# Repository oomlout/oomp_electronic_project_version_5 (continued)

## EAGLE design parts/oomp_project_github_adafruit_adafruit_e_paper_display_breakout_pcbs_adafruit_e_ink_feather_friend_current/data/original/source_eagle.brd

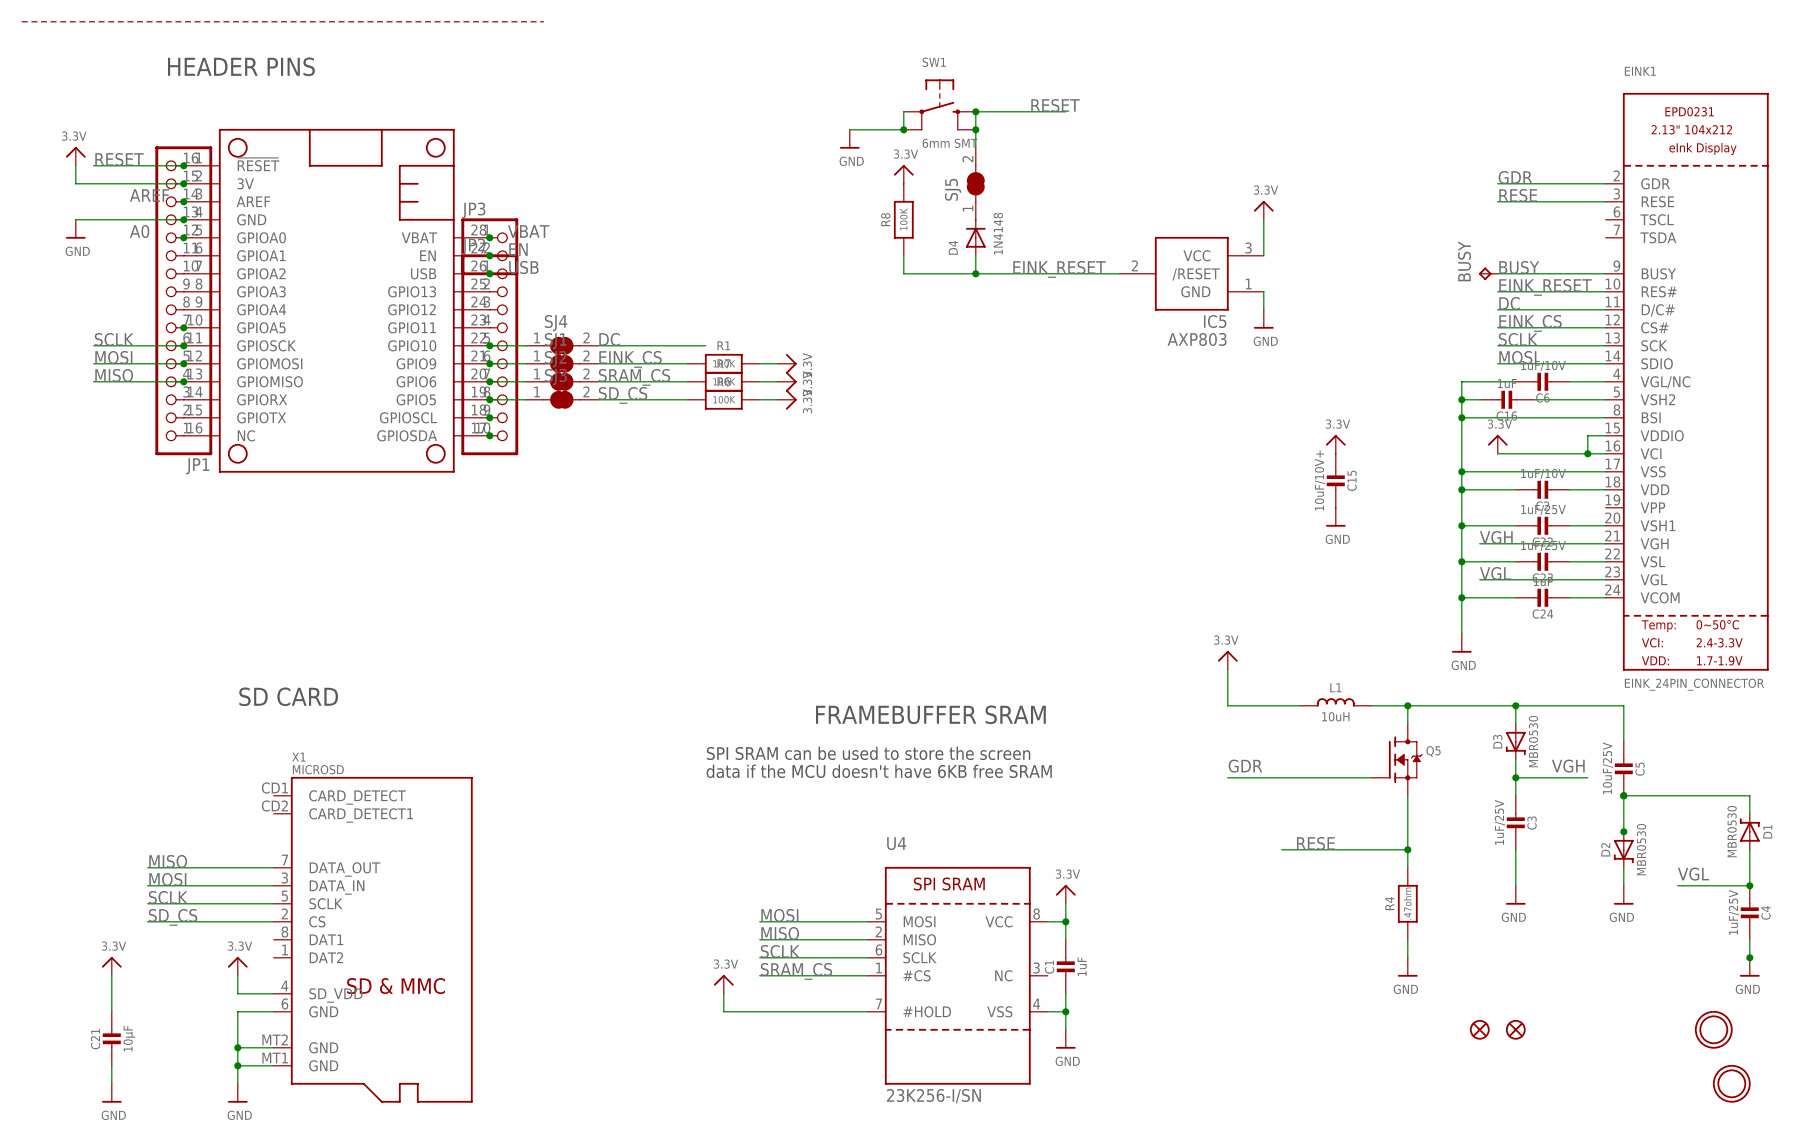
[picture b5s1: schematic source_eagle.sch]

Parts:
BUSY: TPTP15SQ; TP15SQ
C1: 1uF; 0805_10MGAP
C2, C6: 1uF/10V; 0805-NO
C3, C4, C22, C23: 1uF/25V; 0805-NO
C5: 10uF/25V; 0805-NO
C15: 10uF/10V+; 0805-NO
C16, C24: 1uF; 0805-NO
C21: 10µF; 0805-NO
D1, D2, D3: MBR0530; SOD-123
D4: 1N4148; SOD-323F
EINK1: EINK_24PIN_CONNECTOR; EINK_24PIN
FID1, FID3: FIDUCIAL_1MM
IC5: AXP803; SOT23
JP1: HEADER-1X16ROUND; 1X16_ROUND
JP2: HEADER-1X10ROUND; 1X10_ROUND
JP3: HEADER-1X2ROUND; 1X02_ROUND
L1: 10uH; INDUCTOR_4X4MM_NR401
MS1: FEATHERWING_NOHOLES
Q5: IRLML0100; SOT23-3
R1, R6, R7, R8: 100K; 0603-NO
R4: .47ohm; 0805_10MGAP
SJ1, SJ2, SJ3, SJ4, SJ5: SOLDERJUMPER_CLOSED; SOLDERJUMPER_CLOSEDWIRE
SW1: 6mm SMT; BTN_KMR2_4.6X2.8
U4: 23K256-I/SN; SOIC8_150MIL
U$3, U$4: MOUNTINGHOLE2.5; MOUNTINGHOLE_2.5_PLATED
X1: MICROSD

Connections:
3.3V: C1.1, C15.2, C21.1, EINK1.15 (VDDIO), EINK1.16 (VCI), IC5.3 (VCC), JP1.15, L1.P$2 (2), MS1.2 (3V), R1.2, R6.2, R7.2, R8.2, U4.7 (#HOLD), U4.8 (VCC), X1.4 (SD_VDD)
A0: JP1.12, MS1.5 (GPIOA0)
AREF: JP1.14, MS1.3 (AREF)
BUSY: BUSY.TP, EINK1.9 (BUSY)
DC: EINK1.11 (D/C#), SJ4.2
EINK_CS: EINK1.12 (CS#), R1.1, SJ1.2
EINK_RESET: D4.A, EINK1.10 (RES#), IC5.2 (/RESET), R8.1
EN: JP3.2, MS1.27 (EN)
GDR: EINK1.2 (GDR), Q5.1 (G)
GND: C1.2, C2.1, C3.2, C4.2, C6.1, C15.1, C16.1, C21.2, C22.1, C23.1, C24.1, D2.C, EINK1.8 (BSI), EINK1.17 (VSS), IC5.1 (GND), JP1.13, MS1.4 (GND), R4.2, SW1.A, SW1.A' (P1), U4.4 (VSS), X1.6 (GND), X1.MT1 (GND), X1.MT2 (GND)
H: JP2.8, MS1.19 (GPIO5), SJ3.1
I: JP2.7, MS1.20 (GPIO6), SJ2.1
J: JP2.6, MS1.21 (GPIO9), SJ1.1
K: JP2.5, MS1.22 (GPIO10), SJ4.1
MISO: JP1.4, MS1.13 (GPIOMISO), U4.2 (MISO), X1.7 (DATA_OUT)
MOSI: EINK1.14 (SDIO), JP1.5, MS1.12 (GPIOMOSI), U4.5 (MOSI), X1.3 (DATA_IN)
unnamed: JP1.7, MS1.10 (GPIOA5)
unnamed: C5.2, D1.C, D2.A
unnamed: C5.1, D3.A, L1.P$1 (1), Q5.3 (D)
unnamed: C16.2, EINK1.5 (VSH2)
unnamed: C2.2, EINK1.18 (VDD)
unnamed: C22.2, EINK1.20 (VSH1)
unnamed: D4.C, SJ5.1
unnamed: JP1.11, MS1.6 (GPIOA1)
unnamed: C6.2, EINK1.4 (VGL/NC)
unnamed: JP1.10, MS1.7 (GPIOA2)
unnamed: JP1.9, MS1.8 (GPIOA3)
unnamed: JP1.8, MS1.9 (GPIOA4)
unnamed: JP1.3, MS1.14 (GPIORX)
unnamed: JP1.2, MS1.15 (GPIOTX)
unnamed: JP1.1, MS1.16 (NC)
unnamed: JP2.10, MS1.17 (GPIOSDA)
unnamed: JP2.9, MS1.18 (GPIOSCL)
unnamed: JP2.4, MS1.23 (GPIO11)
unnamed: JP2.3, MS1.24 (GPIO12)
unnamed: JP2.2, MS1.25 (GPIO13)
unnamed: C23.2, EINK1.22 (VSL)
unnamed: C24.2, EINK1.24 (VCOM)
RESE: EINK1.3 (RESE), Q5.2 (S), R4.1
RESET: JP1.16, MS1.1 (!RESET), SJ5.2, SW1.B (S), SW1.B' (S1)
SCLK: EINK1.13 (SCK), JP1.6, MS1.11 (GPIOSCK), U4.6 (SCLK), X1.5 (SCLK)
SD_CS: R6.1, SJ3.2, X1.2 (CS)
SRAM_CS: R7.1, SJ2.2, U4.1 (#CS)
USB: JP2.1, MS1.26 (USB)
VBAT: JP3.1, MS1.28 (VBAT)
VGH: C3.1, D3.C, EINK1.21 (VGH)
VGL: C4.1, D1.A, EINK1.23 (VGL)

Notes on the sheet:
HEADER PINS
FRAMEBUFFER SRAM
SPI SRAM can be used to store the screen
data if the MCU doesn't have 6KB free SRAM
SD CARD

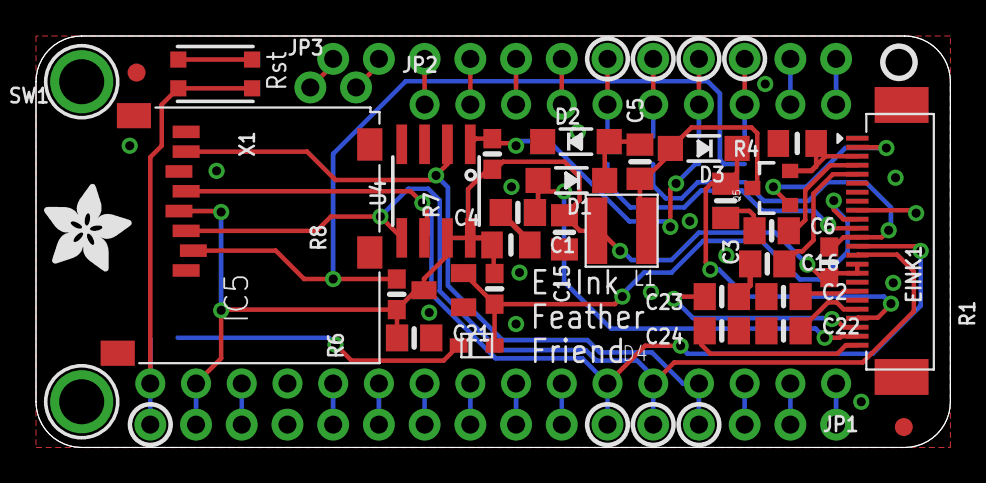
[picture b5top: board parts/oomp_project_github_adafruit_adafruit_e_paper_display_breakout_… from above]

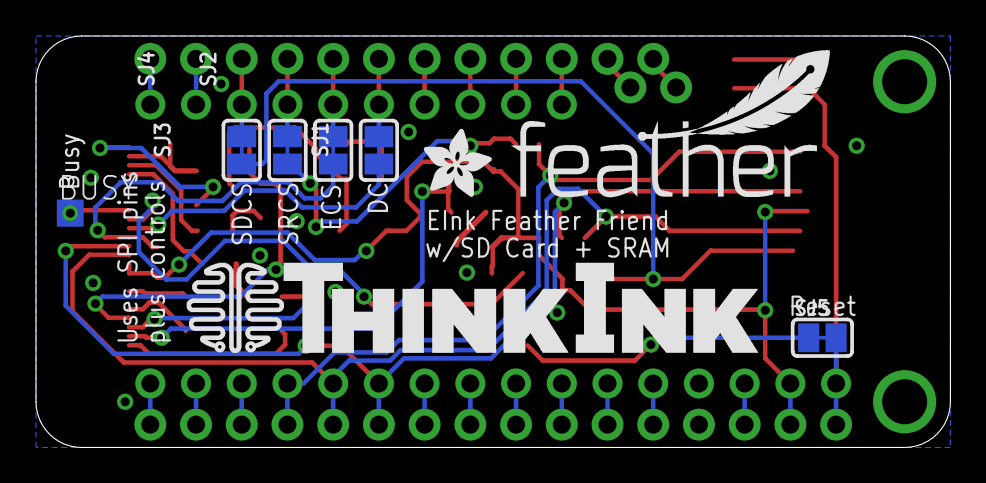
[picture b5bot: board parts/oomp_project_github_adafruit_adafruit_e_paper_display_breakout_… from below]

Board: 2 copper layers, 50.8 x 22.9 mm, 47 parts (9 on the bottom side), 47 nets.

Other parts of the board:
U$5: THINKINK_1.25IN
U$6: FEATHERLOGO_MED
U$8: ADAFRUIT_5MM
U$9: PCBFEAT-REV-040
U$17: ADAFRUIT_3.5MM

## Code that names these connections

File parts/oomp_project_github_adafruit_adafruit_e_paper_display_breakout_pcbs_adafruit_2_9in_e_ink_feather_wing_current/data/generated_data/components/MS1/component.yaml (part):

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        pin_number: TP
        pin_name: TP
    - number: '19'
      name: GPIO5
      electrical_type: bidirectional
      graphic_style: line
      local_position:
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      connected_to:
      - reference: MS1
        pin_number: 19B
        pin_name: GPIO5
      - reference: SJ3
        pin_number: '1'
        pin_name: '1'
    - number: 19B
      name: GPIO5
      electrical_type: bidirectional
      graphic_style: line
      local_position:
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      connected_to:
      - reference: MS1
        pin_number: '19'
        pin_name: GPIO5
      - reference: SJ3
        pin_number: '1'
        pin_name: '1'
    - number: '20'
      name: GPIO6
      electrical_type: bidirectional
      graphic_style: line
      local_position:
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      connected_to:
      - reference: MS1
        pin_number: 20B
        pin_name: GPIO6
      - reference: SJ2
        pin_number: '1'
        pin_name: '1'
    - number: 20B
      name: GPIO6
      electrical_type: bidirectional
      graphic_style: line
      local_position:
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      connected_to:
      - reference: MS1
        pin_number: '20'
        pin_name: GPIO6
      - reference: SJ2
        pin_number: '1'
        pin_name: '1'
    - number: '21'
      name: GPIO9
      electrical_type: bidirectional
      graphic_style: line
      local_position:
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      connected_to:
      - reference: MS1
        pin_number: 21B
        pin_name: GPIO9
      - reference: SJ1
        pin_number: '1'
        pin_name: '1'
    - number: 21B
      name: GPIO9
      electrical_type: bidirectional
      graphic_style: line
      local_position:
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      connected_to:
      - reference: MS1
        pin_number: '21'
        pin_name: GPIO9
      - reference: SJ1
        pin_number: '1'
        pin_name: '1'
    - number: '22'
      name: GPIO10
      electrical_type: bidirectional
      graphic_style: line
      local_position:
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      connected_to:
      - reference: MS1
        pin_number: 22B
        pin_name: GPIO10
      - reference: SJ4
        pin_number: '1'
        pin_name: '1'
    - number: 22B
      name: GPIO10
      electrical_type: bidirectional
      graphic_style: line
      local_position:
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      connected_to:
      - reference: MS1
        pin_number: '22'
        pin_name: GPIO10
      - reference: SJ4
        pin_number: '1'
        pin_name: '1'
    - number: '23'
      name: GPIO11
      electrical_type: bidirectional
      graphic_style: line
      local_position:
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      connected_to:
      - reference: MS1
        pin_number: 23B
        pin_name: GPIO11
      - reference: SW1
        pin_number: '1'
        pin_name: P
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        pin_number: TP
        pin_name: TP
    - number: 23B
      name: GPIO11
      electrical_type: bidirectional
      graphic_style: line
      local_position:
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      connected_to:
      - reference: MS1
        pin_number: '23'
        pin_name: GPIO11
      - reference: SW1
        pin_number: '1'
        pin_name: P
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        pin_number: TP
        pin_name: TP
    - number: '24'
      name: GPIO12
      electrical_type: bidirectional
      graphic_style: line
      local_position:
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      connected_to:
      - reference: MS1
        pin_number: 24B
        pin_name: GPIO12
      - reference: SW2
        pin_number: '1'
        pin_name: P
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        pin_number: TP
        pin_name: TP
    - number: 24B
      name: GPIO12
      electrical_type: bidirectional
      graphic_style: line
      local_position:
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      connected_to:
      - reference: MS1
        pin_number: '24'
        pin_name: GPIO12
      - reference: SW2
        pin_number: '1'
        pin_name: P
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        pin_number: TP
        pin_name: TP
    - number: '25'
      name: GPIO13
      electrical_type: bidirectional
      graphic_style: line
      local_position:
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      connected_to:
      - reference: MS1
        pin_number: 25B
        pin_name: GPIO13
      - reference: SW4
        pin_number: '1'
        pin_name: P
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        pin_number: TP
        pin_name: TP
    - number: 25B
      name: GPIO13
      electrical_type: bidirectional
      graphic_style: line
      local_position:
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      connected_to:
      - reference: MS1
        pin_number: '25'
        pin_name: GPIO13
      - reference: SW4
        pin_number: '1'
        pin_name: P
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    pin_name: GPIOSCL
  - reference: MS1
    pin_number: '19'
    pin_name: GPIO5
  - reference: MS1
    pin_number: 19B
    pin_name: GPIO5
  - reference: MS1
    pin_number: 1B
    pin_name: ~{RESET}
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    pin_name: 3V
  - reference: MS1
    pin_number: '20'
    pin_name: GPIO6
  - reference: MS1
    pin_number: 20B
    pin_name: GPIO6
  - reference: MS1
    pin_number: '21'
    pin_name: GPIO9
  - reference: MS1
    pin_number: 21B
    pin_name: GPIO9
  - reference: MS1
    pin_number: '22'
    pin_name: GPIO10
  - reference: MS1
    pin_number: 22B
    pin_name: GPIO10
  - reference: MS1
    pin_number: '23'
    pin_name: GPIO11
  - reference: MS1
    pin_number: 23B
    pin_name: GPIO11
  - reference: MS1
    pin_number: '24'
    pin_name: GPIO12
  - reference: MS1
    pin_number: 24B
    pin_name: GPIO12
  - reference: MS1
    pin_number: '25'
    pin_name: GPIO13
  - reference: MS1
    pin_number: 25B
    pin_name: GPIO13
  - reference: MS1
    pin_number: '26'
    pin_name: USB
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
